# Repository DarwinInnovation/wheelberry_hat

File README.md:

# wheelberry_hat
Raspberry PI HAT for Wheelchair control

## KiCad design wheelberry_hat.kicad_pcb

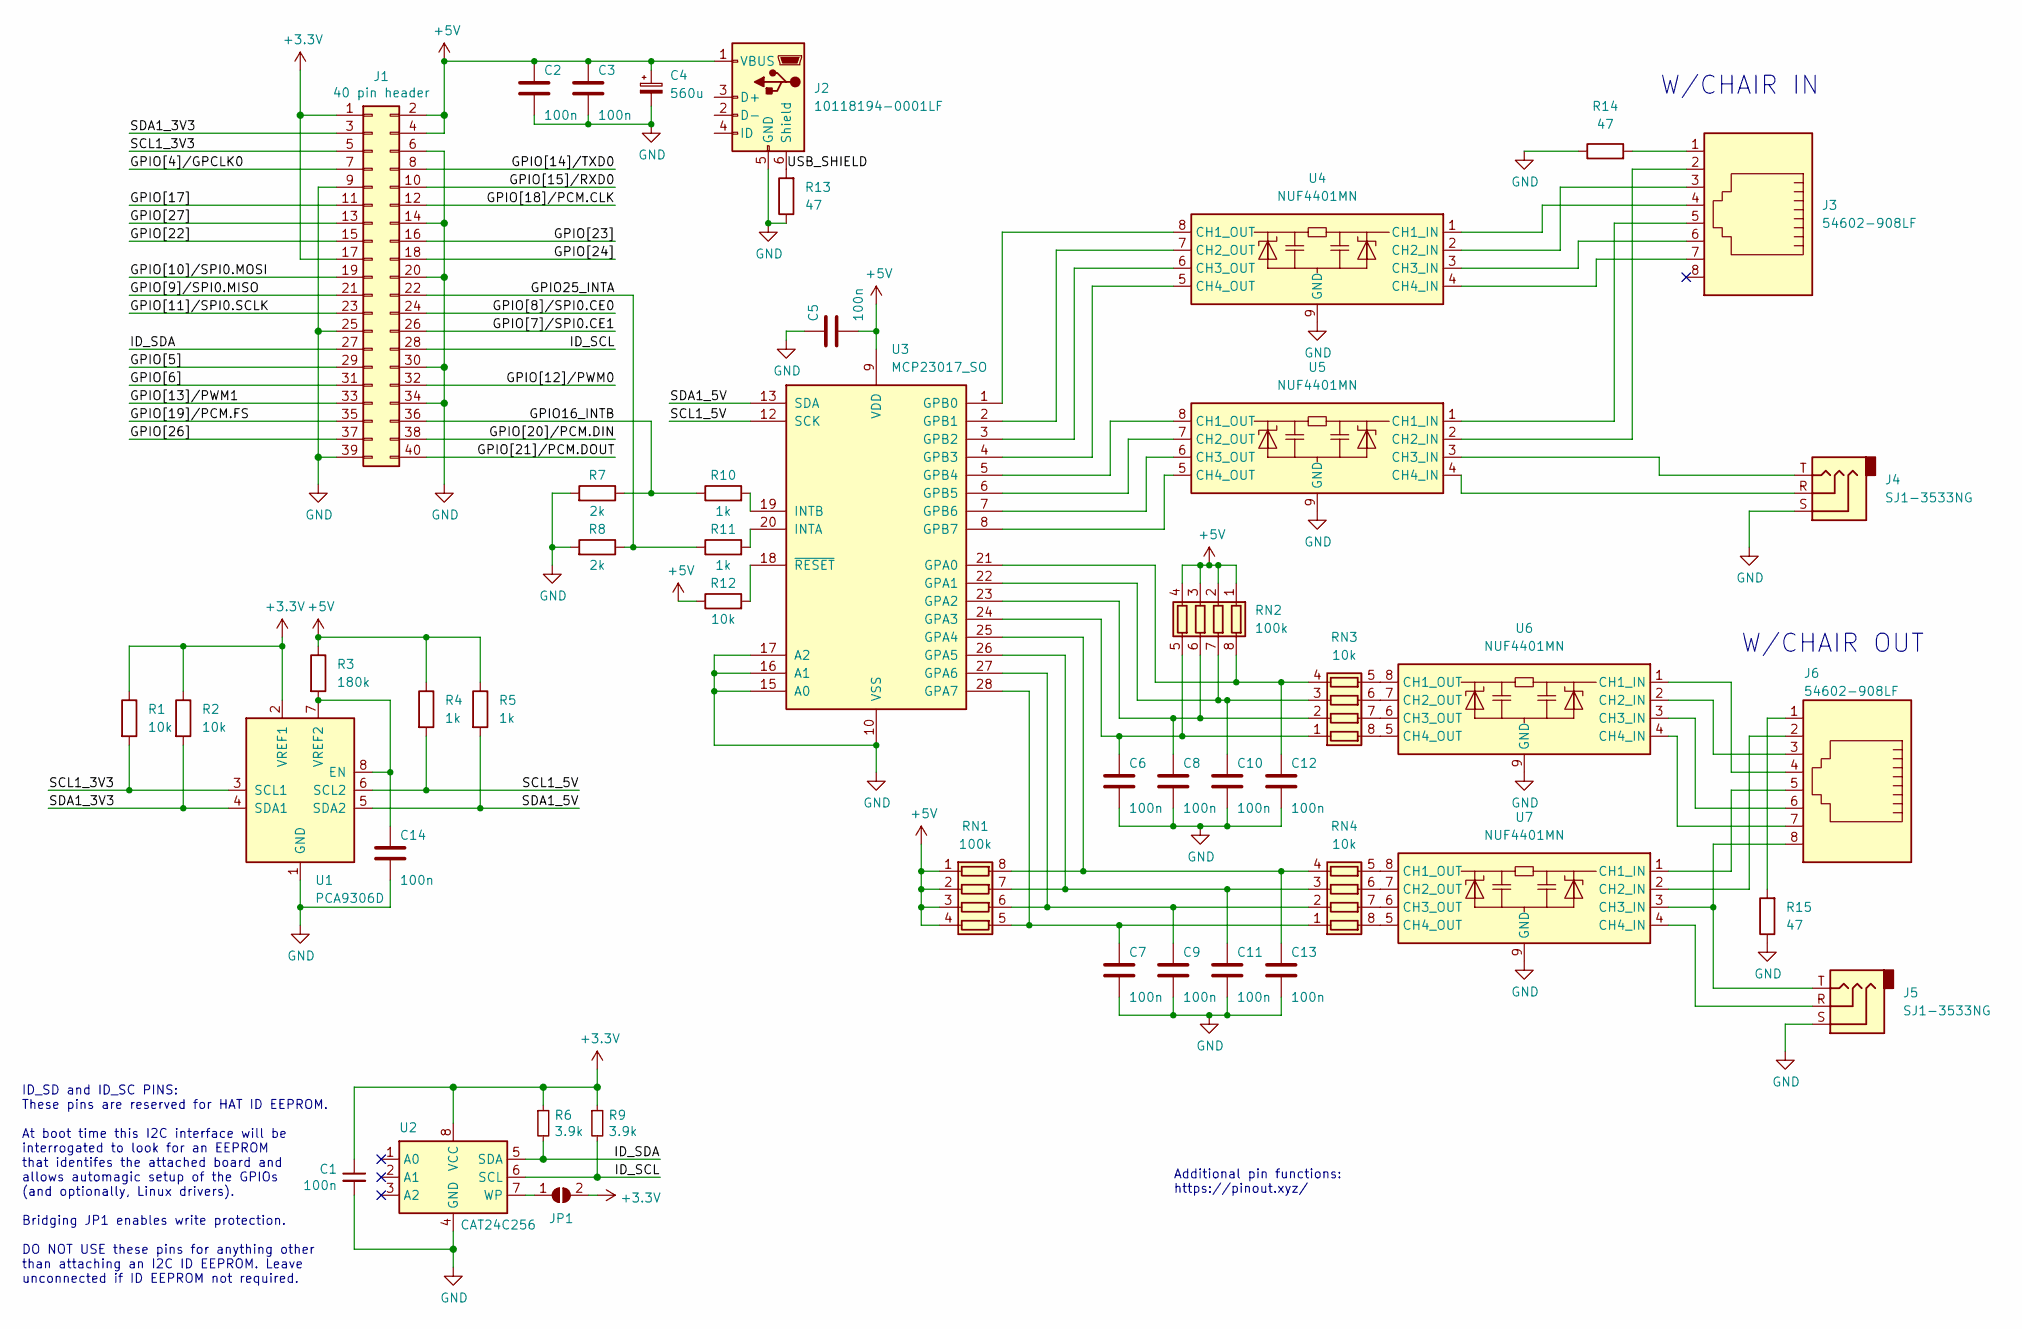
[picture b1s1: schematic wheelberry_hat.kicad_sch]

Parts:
C1, C2, C3, C5, C6, C7, C8, C9, C10, C11, C12, C13, C14: 100n; C_0805_2012Metric; LCSC C49678
C4: 560u; CP_Radial_D10.0mm_P2.50mm_P5.00mm; MPN 20SEPF560M
J1: 40 pin header; PinSocket_2x20_P2.54mm_Vertical
J2: 10118194-0001LF; USB_Micro-B_Amphenol_10118194_Horizontal; MPN 10118194-0001LF; LCSC C132563
J3, J6: 54602-908LF; RJ45_Amphenol_54602-x08_Horizontal; MPN 54602-908LF
J4, J5: SJ1-3533NG; Jack_3.5mm_CUI_SJ1-3533NG_Horizontal; MPN SJ1-3533NG
JP1: 2 pin header; PinHeader_1x02_P2.54mm_Vertical
R1, R2, R12: 10k; R_0805_2012Metric; LCSC C17414
R3: 180k; R_0805_2012Metric; LCSC C17501
R4, R5, R10, R11: 1k; R_0805_2012Metric; LCSC C17513
R6, R9: 3.9k; R_0805_2012Metric; LCSC C17614
R7, R8: 2k; R_0805_2012Metric; LCSC C17604
R13, R14, R15: 47; R_0805_2012Metric; LCSC C17714
RN1, RN2: 100k; R_Array_Convex_4x0603; MPN YC164-FR-0710KL; LCSC C192933
RN3, RN4: 10k; R_Array_Convex_4x0603; MPN YC164-FR-0710KL; LCSC C110924
U1: PCA9306D; SO-8_3.9x4.9mm_P1.27mm; MPN PCA9306D,118; LCSC C2677369
U2: CAT24C256; SOIC-8_3.9x4.9mm_P1.27mm; MPN CAT24C128WI-GT3; LCSC C81195
U3: MCP23017_SO; SOIC-28W_7.5x17.9mm_P1.27mm; MPN MCP23017-SO
U4, U5, U6, U7: NUF4401MN; DFN-8-1EP_2x2mm_P0.5mm_EP0.7x1.3mm; MPN NUF4401MNT1G; LCSC C479731

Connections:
+3V3: C1.1, J1.1, J1.17, JP1.2 (B), R1.1, R2.1, R6.1, R9.1, U1.2 (VREF1), U2.8 (VCC)
+5V: C2.1, C3.1, C4.1, C5.2, J1.2, J1.4, J2.1 (VBUS), R3.1, R4.1, R5.1, R12.1, RN1.1 (R1.1), RN1.2 (R2.1), RN1.3 (R3.1), RN1.4 (R4.1), RN2.1 (R1.1), RN2.2 (R2.1), RN2.3 (R3.1), RN2.4 (R4.1), U3.9 (VDD)
/GPIO16_INTB: J1.36, R7.1, R10.1
/GPIO25_INTA: J1.22, R8.1, R11.1
/GPIO[4]/GPCLK0: J1.7
/GPIO[5]: J1.29
/GPIO[6]: J1.31
/GPIO[7]/SPI0.CE1: J1.26
/GPIO[8]/SPI0.CE0: J1.24
/GPIO[9]/SPI0.MISO: J1.21
/GPIO[10]/SPI0.MOSI: J1.19
/GPIO[11]/SPI0.SCLK: J1.23
/GPIO[12]/PWM0: J1.32
/GPIO[13]/PWM1: J1.33
/GPIO[14]/TXD0: J1.8
/GPIO[15]/RXD0: J1.10
/GPIO[17]: J1.11
/GPIO[18]/PCM.CLK: J1.12
/GPIO[19]/PCM.FS: J1.35
/GPIO[20]/PCM.DIN: J1.38
/GPIO[21]/PCM.DOUT: J1.40
/GPIO[22]: J1.15
/GPIO[23]: J1.16
/GPIO[24]: J1.18
/GPIO[26]: J1.37
/GPIO[27]: J1.13
/ID_SCL: J1.28, R9.2, U2.6 (SCL)
/ID_SDA: J1.27, R6.2, U2.5 (SDA)
/SCL1_3V3: J1.5, R1.2, U1.3 (SCL1)
/SCL1_5V: R4.2, U1.6 (SCL2), U3.12 (SCK)
/SDA1_3V3: J1.3, R2.2, U1.4 (SDA1)
/SDA1_5V: R5.2, U1.5 (SDA2), U3.13 (SDA)
/USB_SHIELD: J2.6 (Shield), R13.2
GND: C1.2, C2.2, C3.2, C4.2, C5.1, C6.2, C7.2, C8.2, C9.2, C10.2, C11.2, C12.2, C13.2, C14.2, J1.6, J1.9, J1.14, J1.20, J1.25, J1.30, J1.34, J1.39, J2.5 (GND), J4.S, J5.S, R7.2, R8.2, R13.1, R14.1, R15.1, U1.1 (GND), U2.4 (GND), U3.10 (VSS), U3.15 (A0), U3.16 (A1), U3.17 (A2), U4.9 (GND), U5.9 (GND), U6.9 (GND), U7.9 (GND)
unnamed: C6.1, RN2.5 (R4.2), RN3.1 (R1.1), U3.24 (GPA3)
unnamed: C7.1, RN1.5 (R4.2), RN4.1 (R1.1), U3.28 (GPA7)
unnamed: C8.1, RN2.6 (R3.2), RN3.2 (R2.1), U3.23 (GPA2)
unnamed: C9.1, RN1.6 (R3.2), RN4.2 (R2.1), U3.27 (GPA6)
unnamed: C10.1, RN2.7 (R2.2), RN3.3 (R3.1), U3.22 (GPA1)
unnamed: C11.1, RN1.7 (R2.2), RN4.3 (R3.1), U3.26 (GPA5)
unnamed: C12.1, RN2.8 (R1.2), RN3.4 (R4.1), U3.21 (GPA0)
unnamed: C13.1, RN1.8 (R1.2), RN4.4 (R4.1), U3.25 (GPA4)
unnamed: C14.1, R3.2, U1.7 (VREF2), U1.8 (EN)
unnamed: J3.1, R14.2
unnamed: J3.2, U5.2 (CH2_IN)
unnamed: J3.3, U4.2 (CH2_IN)
unnamed: J3.4, U4.1 (CH1_IN)
unnamed: J3.5, U5.1 (CH1_IN)
unnamed: J3.6, U4.3 (CH3_IN)
unnamed: J3.7, U4.4 (CH4_IN)
unnamed: J4.R, U5.4 (CH4_IN)
unnamed: J4.T, U5.3 (CH3_IN)
unnamed: J5.R, U7.4 (CH4_IN)
unnamed: J5.T, J6.8, U7.3 (CH3_IN)
unnamed: J6.1, R15.2
unnamed: J6.2, U7.2 (CH2_IN)
unnamed: J6.3, U6.2 (CH2_IN)
unnamed: J6.4, U6.1 (CH1_IN)
unnamed: J6.5, U7.1 (CH1_IN)
unnamed: J6.6, U6.3 (CH3_IN)
unnamed: J6.7, U6.4 (CH4_IN)
unnamed: JP1.1 (A), U2.7 (WP)
unnamed: R10.2, U3.19 (INTB)
unnamed: R11.2, U3.20 (INTA)
unnamed: R12.2, U3.18 (~RESET)
unnamed: RN3.5 (R4.2), U6.8 (CH1_OUT)
unnamed: RN3.6 (R3.2), U6.7 (CH2_OUT)
unnamed: RN3.7 (R2.2), U6.6 (CH3_OUT)
unnamed: RN3.8 (R1.2), U6.5 (CH4_OUT)
unnamed: RN4.5 (R4.2), U7.8 (CH1_OUT)
unnamed: RN4.6 (R3.2), U7.7 (CH2_OUT)
unnamed: RN4.7 (R2.2), U7.6 (CH3_OUT)
unnamed: RN4.8 (R1.2), U7.5 (CH4_OUT)
unnamed: U3.1 (GPB0), U4.8 (CH1_OUT)
unnamed: U3.2 (GPB1), U4.7 (CH2_OUT)
unnamed: U3.3 (GPB2), U4.6 (CH3_OUT)
unnamed: U3.4 (GPB3), U4.5 (CH4_OUT)
unnamed: U3.5 (GPB4), U5.8 (CH1_OUT)
unnamed: U3.6 (GPB5), U5.7 (CH2_OUT)
unnamed: U3.7 (GPB6), U5.6 (CH3_OUT)
unnamed: U3.8 (GPB7), U5.5 (CH4_OUT)

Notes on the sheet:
Additional pin functions: https://pinout.xyz/
ID_SD and ID_SC PINS: These pins are reserved for HAT ID EEPROM. At boot time this I2C interface will be interrogated to look for an EEPROM that identifes the attached board and allows automagic setup of the GPIOs (and optionally, Linux drivers). Bridging JP1 enables write protection. DO NOT USE th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
W/CHAIR OUT
W/CHAIR IN

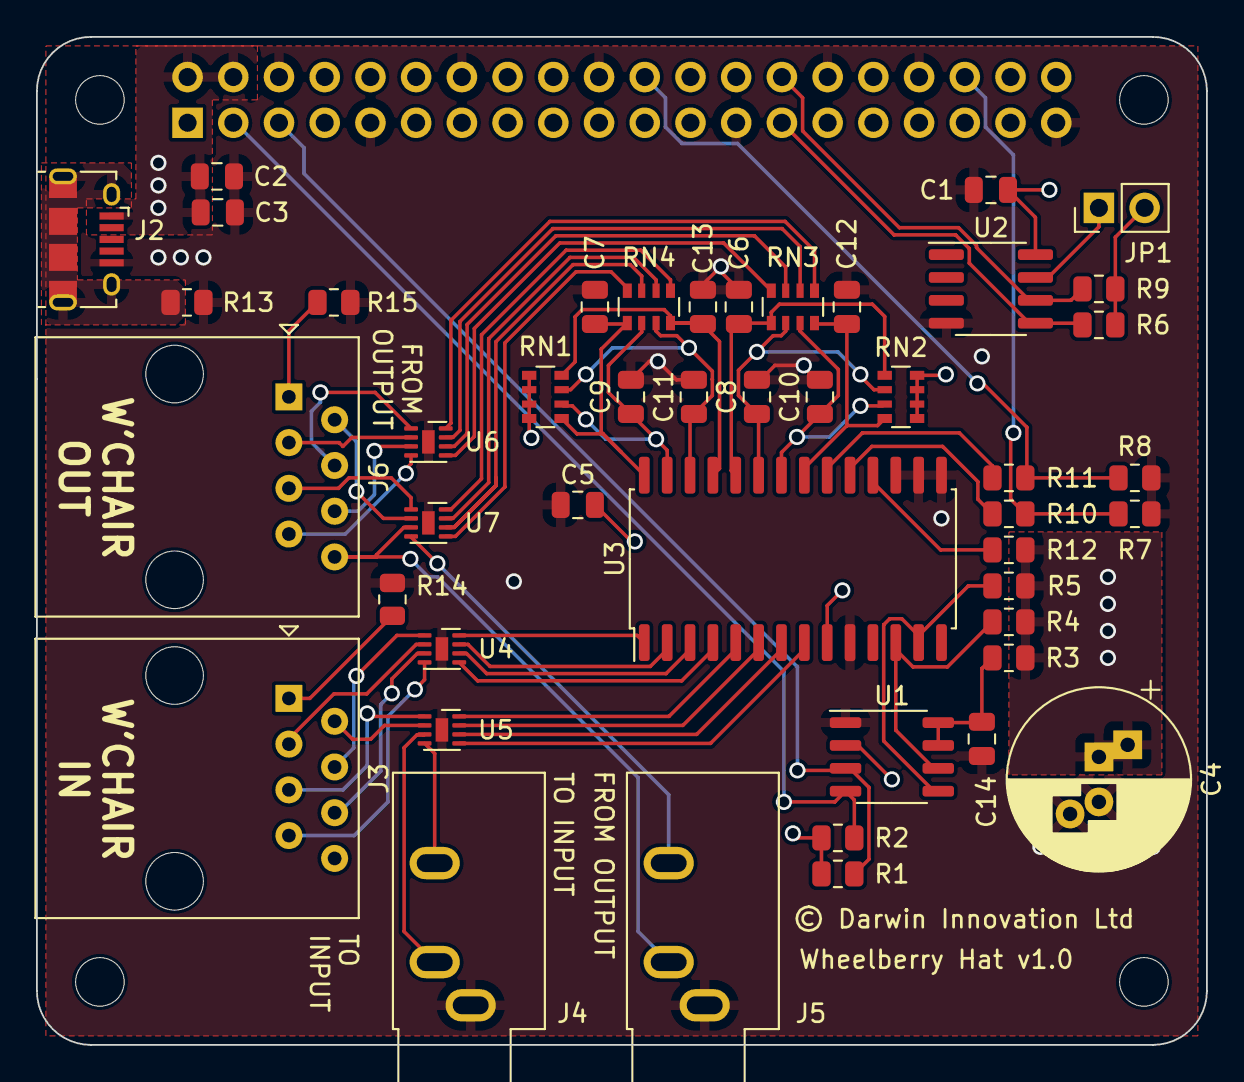
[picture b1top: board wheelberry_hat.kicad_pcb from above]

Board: 4 copper layers, 65.0 x 56.0 mm, 51 parts (1 on the bottom side), 59 nets.

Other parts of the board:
MH1, MH2, MH3, MH4: MountingHole_2.7mm_M2.5

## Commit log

2022-09-26 Add v1.0
2022-10-25 add kicad6 temps
2022-10-25 toggle bit 0
2022-11-01 update tests

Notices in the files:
wheelberry_hat.kicad_pcb:
© Darwin Innovation Ltd
